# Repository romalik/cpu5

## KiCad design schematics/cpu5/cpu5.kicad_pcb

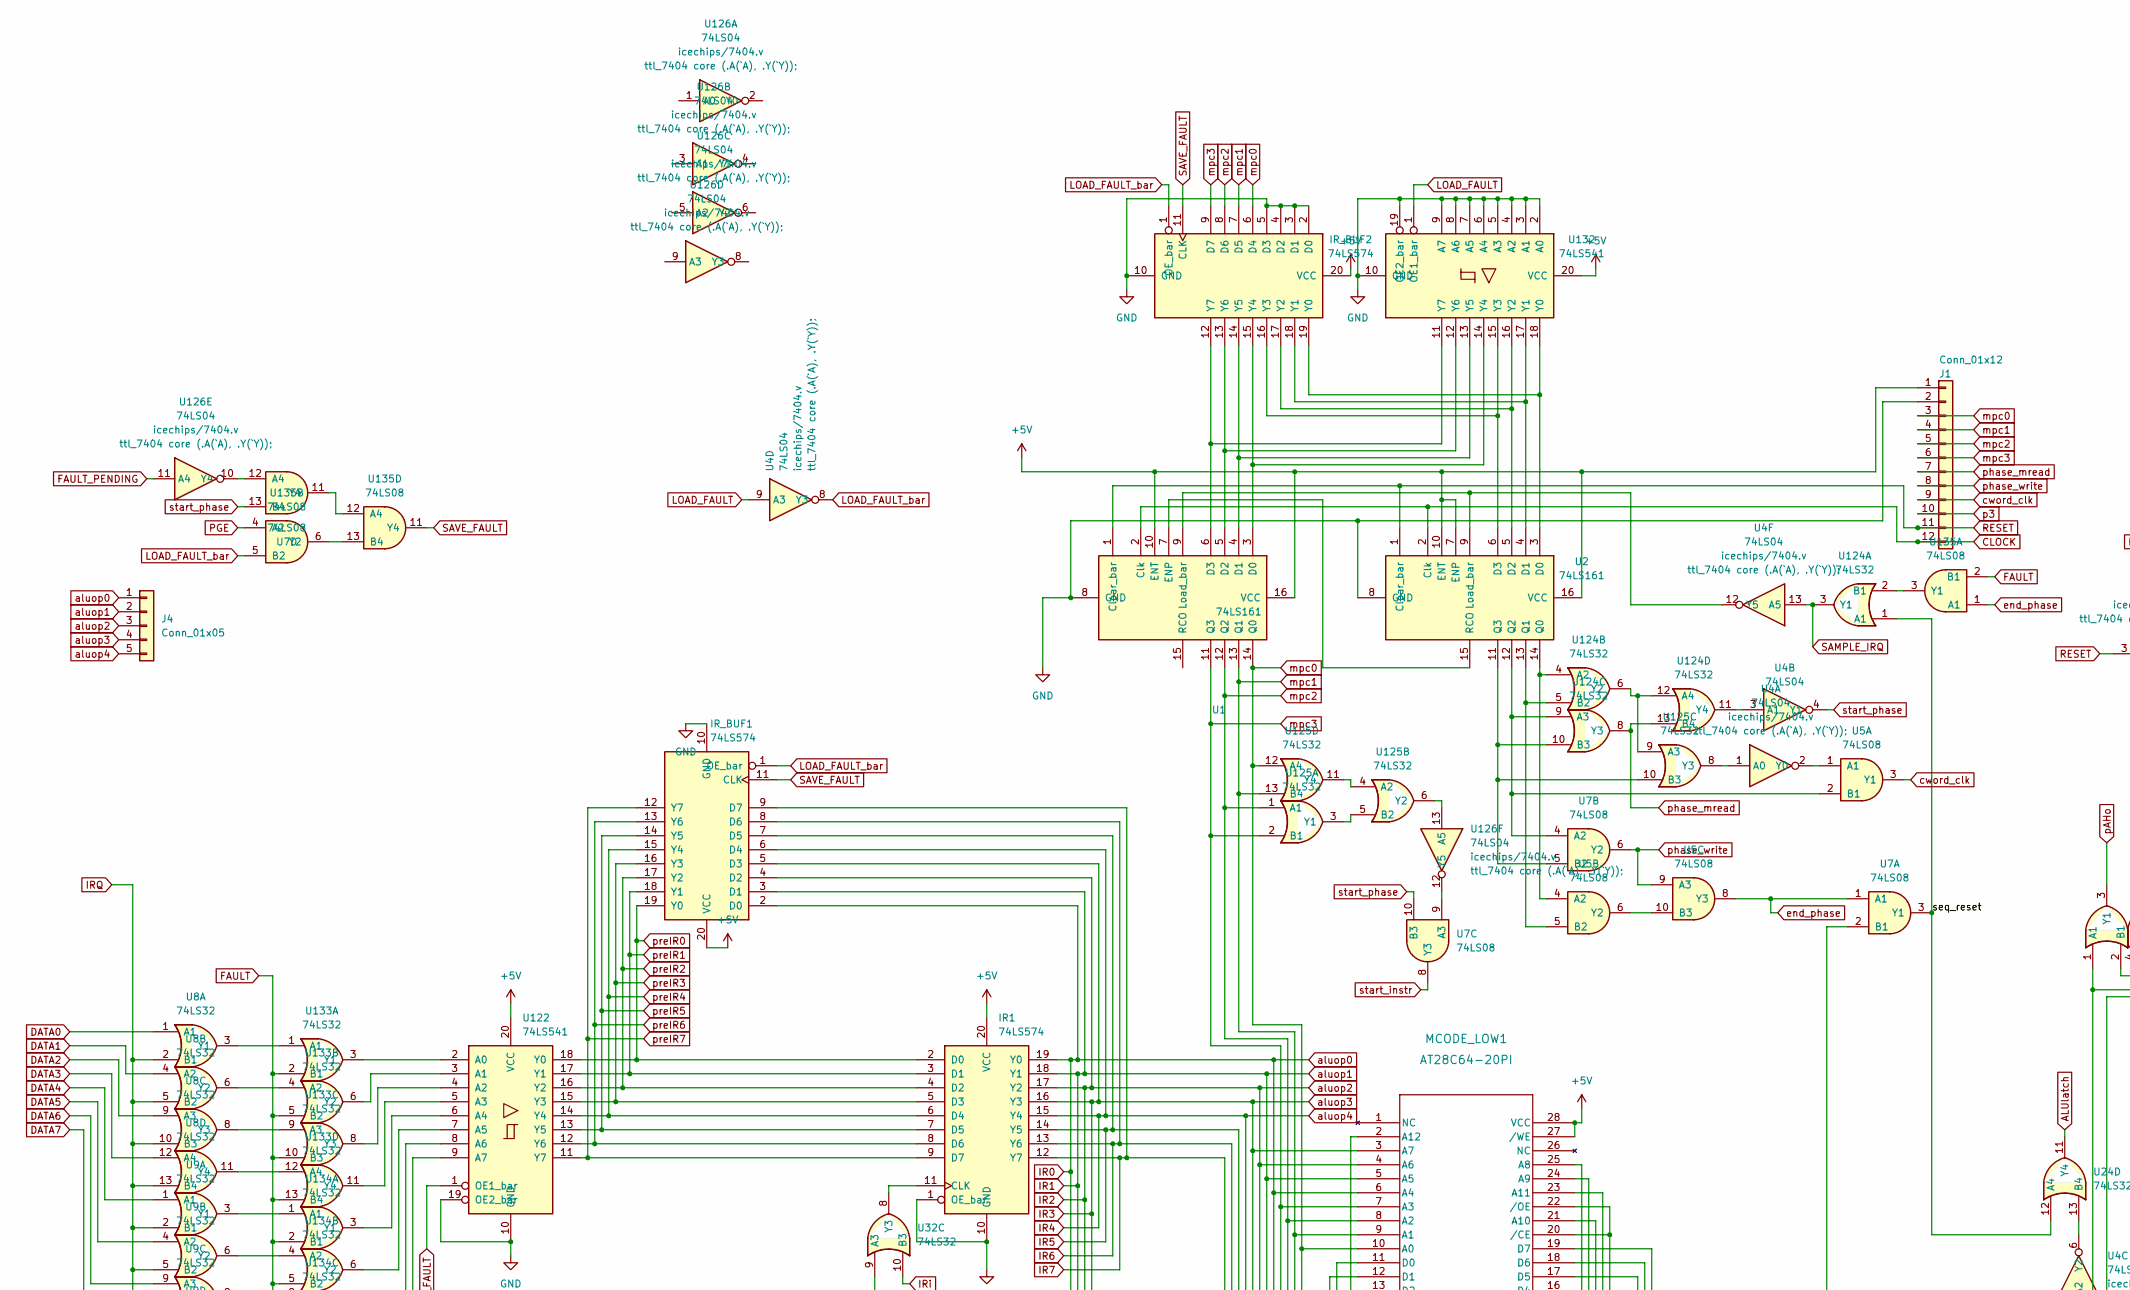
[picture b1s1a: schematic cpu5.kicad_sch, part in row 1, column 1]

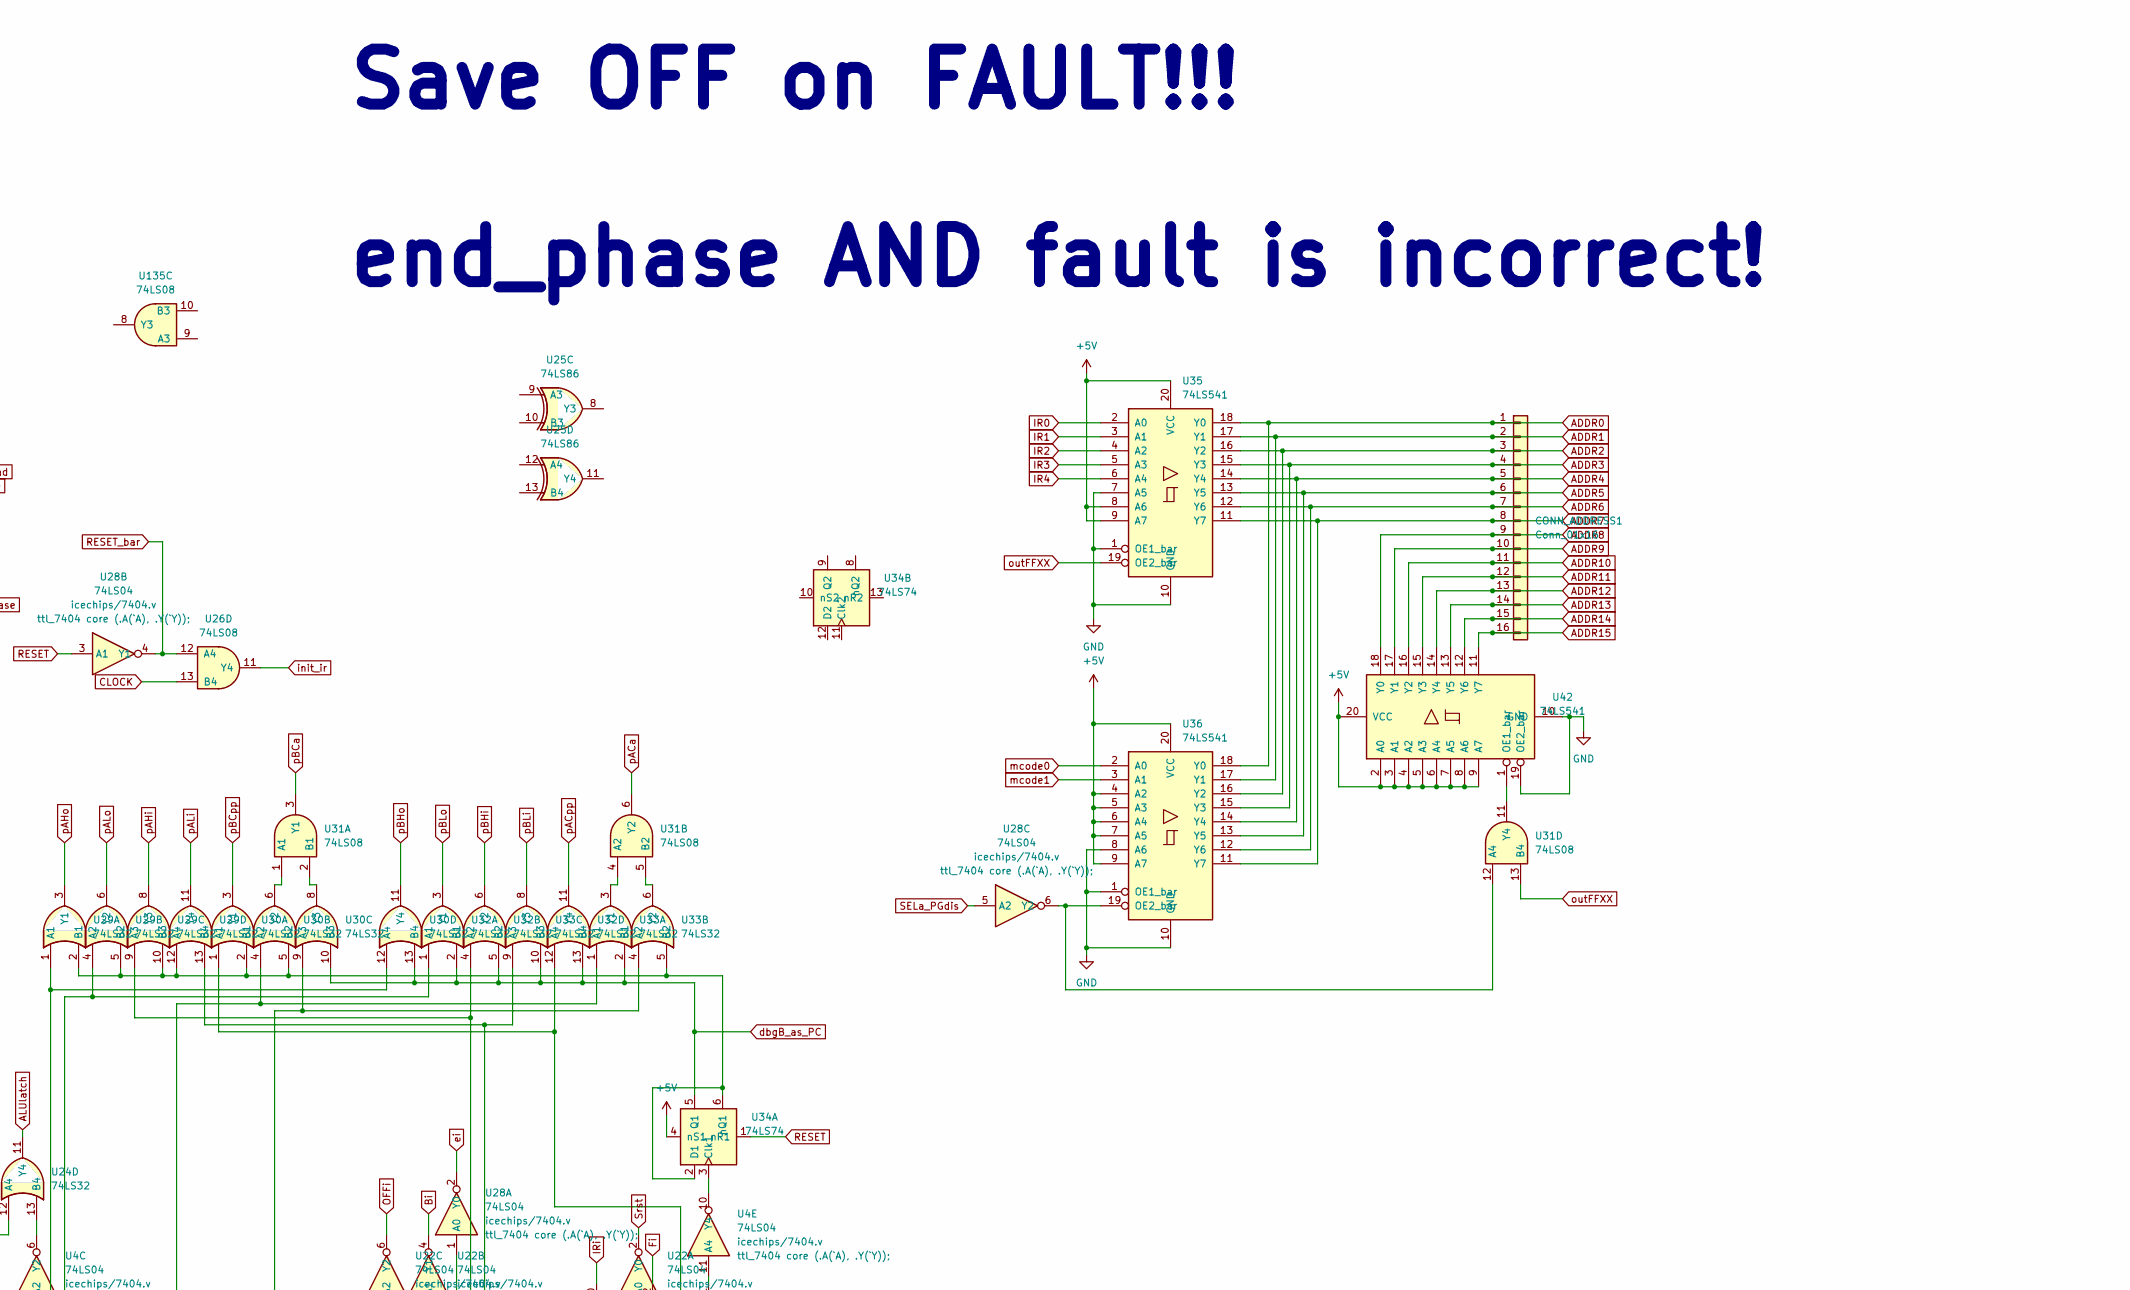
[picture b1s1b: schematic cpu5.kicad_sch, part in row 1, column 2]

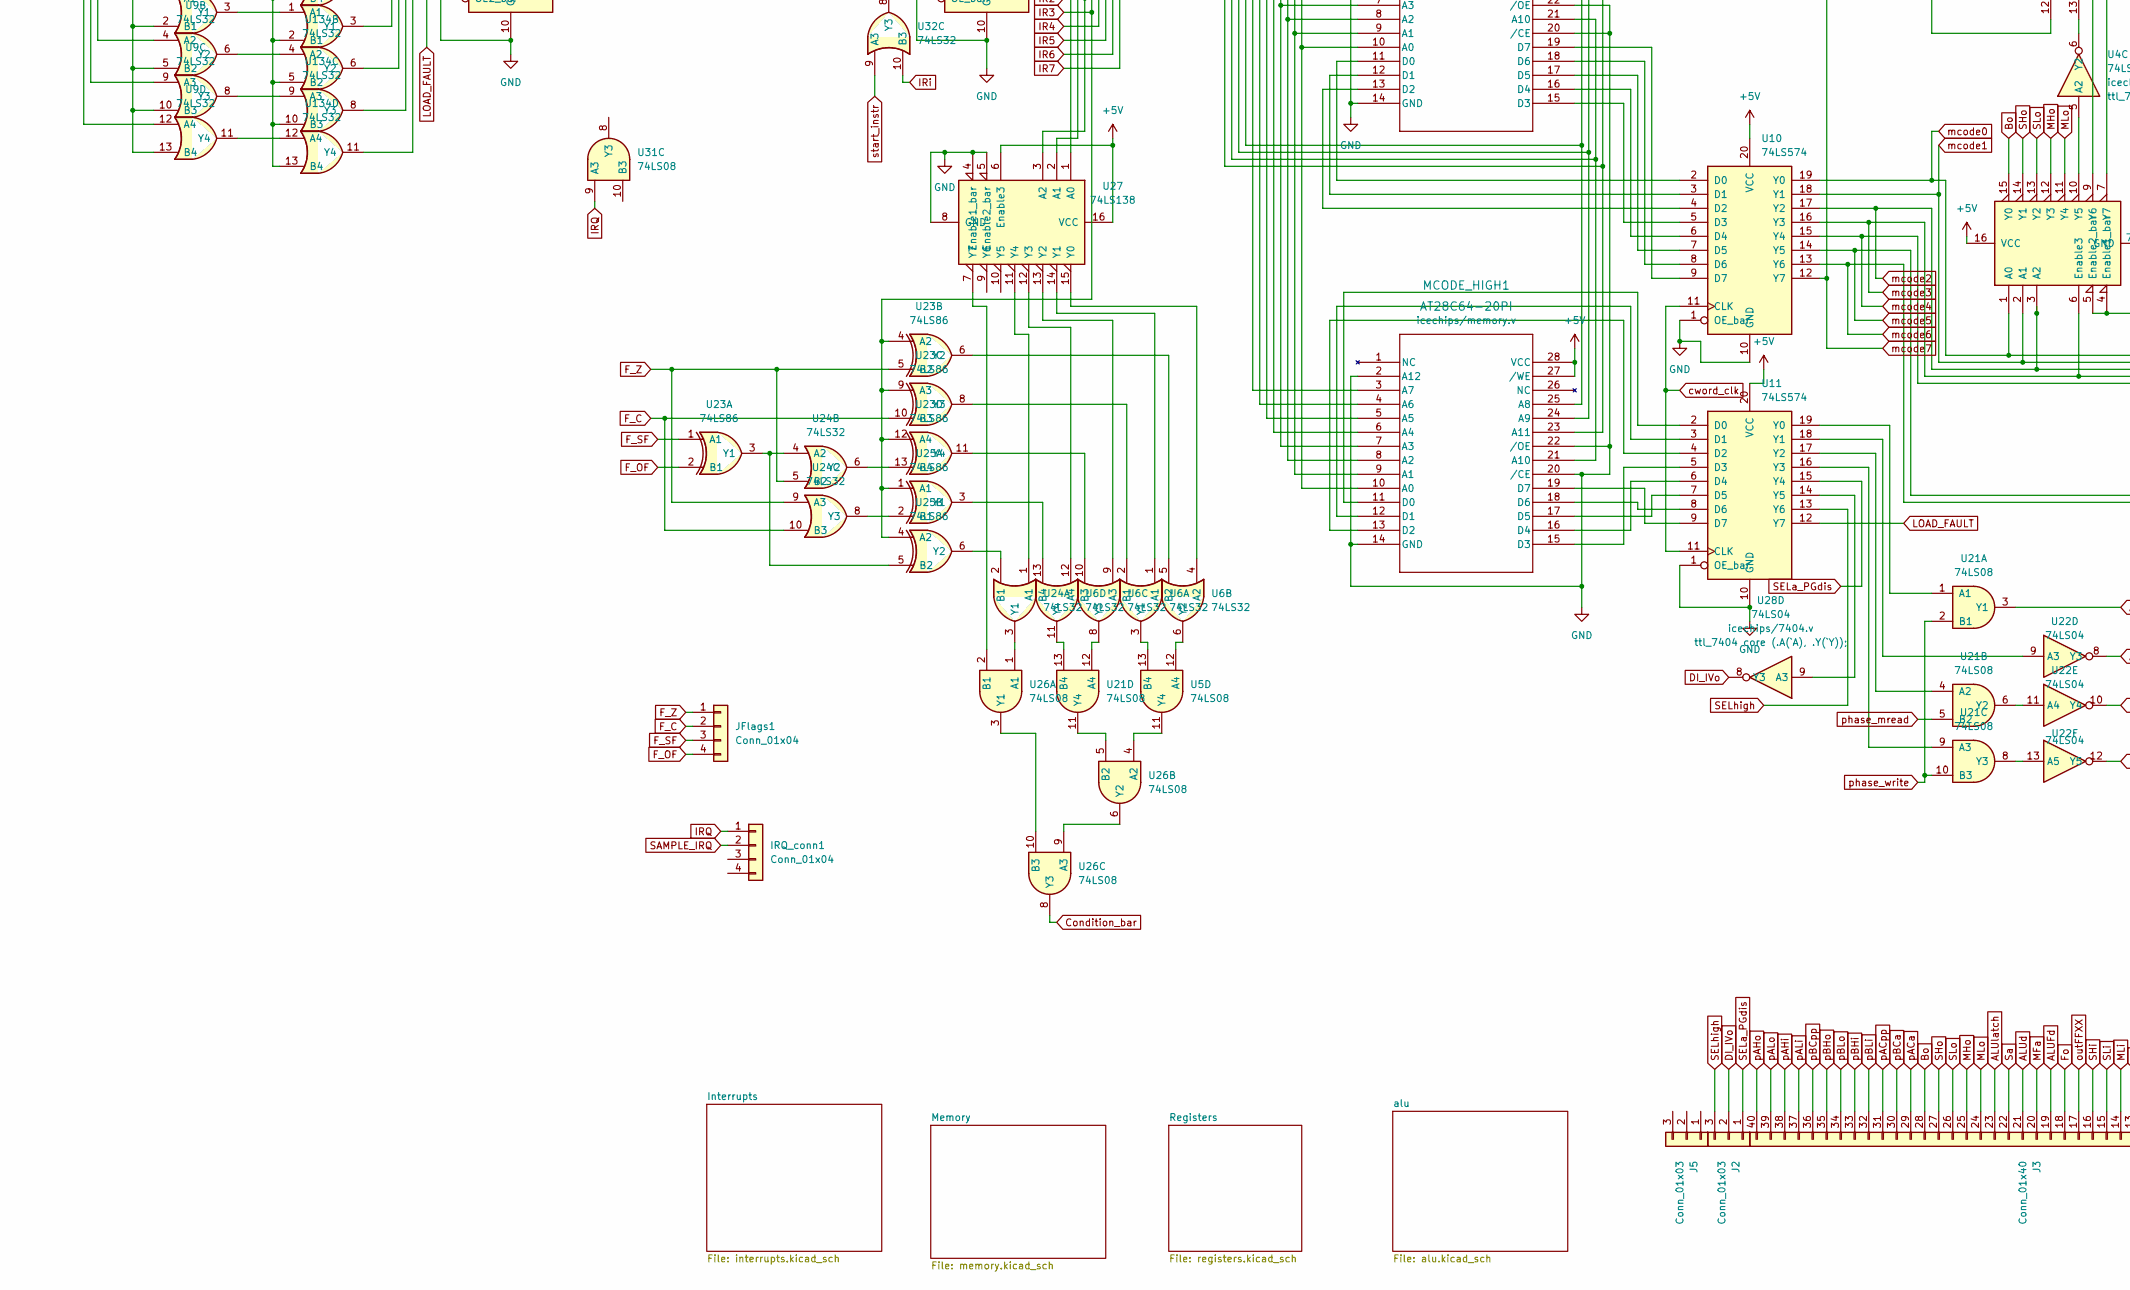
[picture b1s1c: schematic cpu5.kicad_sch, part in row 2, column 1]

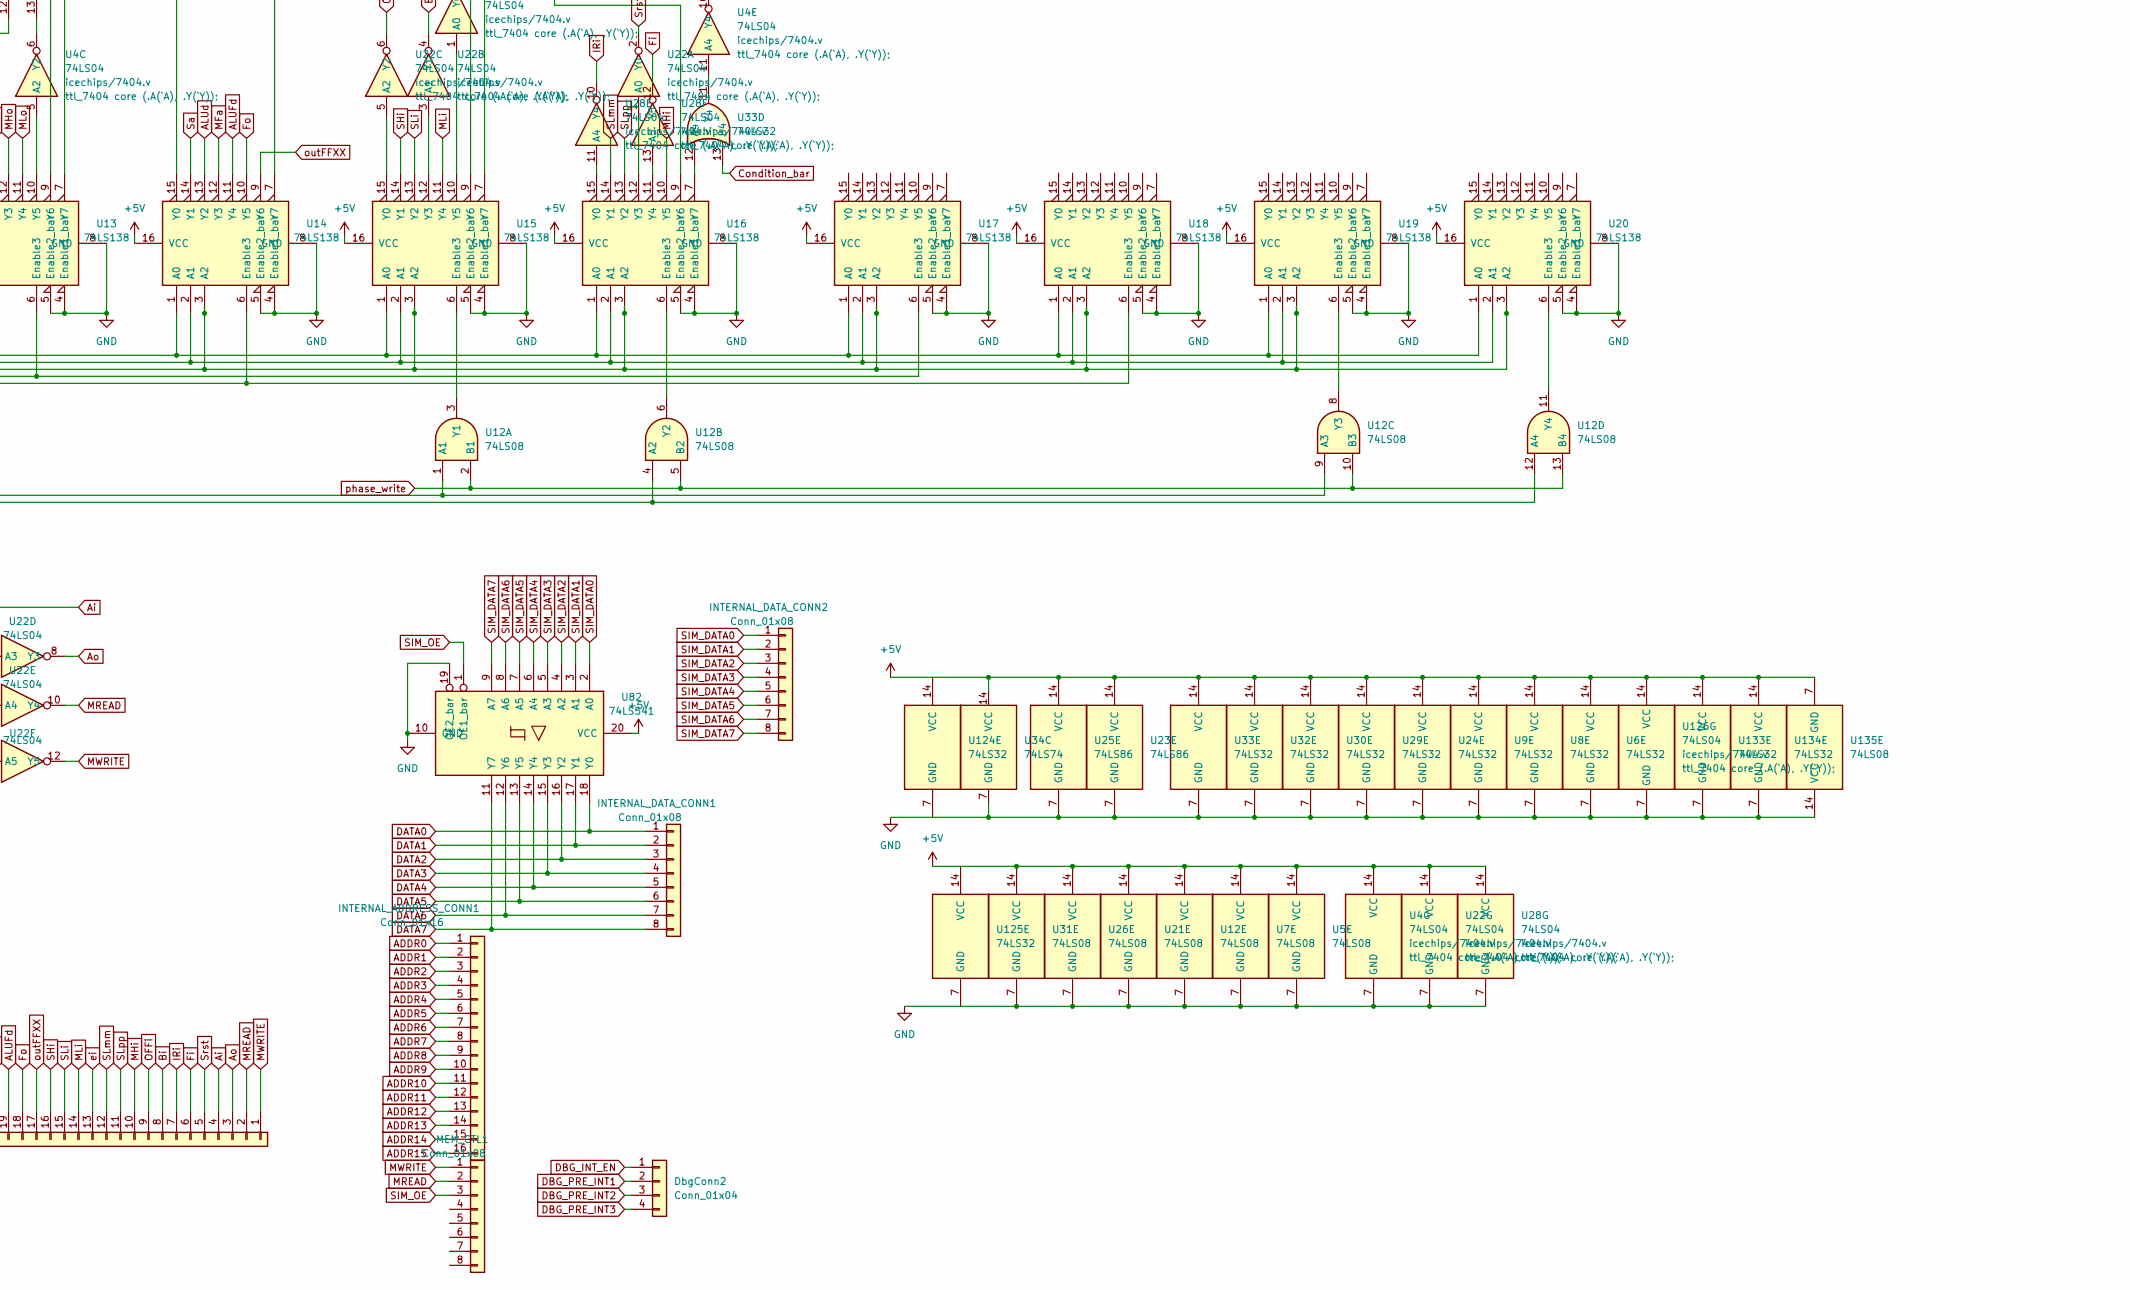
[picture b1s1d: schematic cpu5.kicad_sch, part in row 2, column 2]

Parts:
CONN_ADDRESS1: Conn_01x16; PinHeader_1x16_P2.54mm_Vertical
DbgConn2: Conn_01x04; PinHeader_1x04_P1.00mm_Vertical
INTERNAL_ADDRESS_CONN1: Conn_01x16; PinHeader_1x16_P2.54mm_Vertical
INTERNAL_DATA_CONN1, INTERNAL_DATA_CONN2: Conn_01x08; PinHeader_1x08_P2.54mm_Vertical
IR1: 74LS574; DIP-20_W7.62mm
IRQ_conn1: Conn_01x04; PinHeader_1x04_P1.00mm_Vertical
IR_BUF1, IR_BUF2: 74LS574; DIP-20_W7.62mm
J1: Conn_01x12; PinHeader_1x12_P2.54mm_Vertical
J2, J5: Conn_01x03; PinHeader_1x03_P2.54mm_Vertical
J3: Conn_01x40; PinHeader_1x40_P2.54mm_Vertical
J4: Conn_01x05; PinHeader_1x05_P2.54mm_Vertical
JFlags1: Conn_01x04; PinHeader_1x04_P1.00mm_Vertical
MCODE_HIGH1: AT28C64-20PI; DIP-28_W15.24mm
MCODE_LOW1: AT28C64-20PI; DIP-28_W15.24mm
MEM_CTL1: Conn_01x08; PinHeader_1x08_P2.54mm_Vertical
U1, U2: 74LS161; DIP-16_W7.62mm
U4, U22, U28, U126: 74LS04; DIP-14_W7.62mm
U5, U7, U12, U21, U26, U31, U135: 74LS08; DIP-14_W7.62mm
U6, U8, U9, U24, U29, U30, U32, U33, U124, U125, U133, U134: 74LS32; DIP-14_W7.62mm
U10, U11: 74LS574; DIP-20_W7.62mm
U13, U14, U15, U16, U17, U18, U19, U20, U27: 74LS138; DIP-16_W7.62mm
U23, U25: 74LS86; DIP-14_W7.62mm
U34: 74LS74; DIP-14_W7.62mm
U35, U36, U42, U82, U122, U132: 74LS541; DIP-20_W7.62mm

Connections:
+5V: IR1.20 (VCC), IR_BUF1.20 (VCC), IR_BUF2.20 (VCC), J1.1, MCODE_HIGH1.27 (/WE), MCODE_HIGH1.28 (VCC), MCODE_LOW1.27 (/WE), MCODE_LOW1.28 (VCC), U1.10 (ENT), U1.16 (VCC), U2.7 (ENP), U2.10 (ENT), U2.16 (VCC), U4.14 (VCC), U5.14 (VCC), U6.14 (VCC), U7.14 (VCC), U8.14 (VCC), U9.14 (VCC), U10.20 (VCC), U11.20 (VCC), U12.14 (VCC), U13.16 (VCC), U14.16 (VCC), U15.16 (VCC), U16.16 (VCC), U17.16 (VCC), U18.16 (VCC), U19.16 (VCC), U20.16 (VCC), U21.14 (VCC), U22.14 (VCC), U23.14 (VCC), U24.14 (VCC), U25.14 (VCC), U26.14 (VCC), U27.6 (Enable3), U27.16 (VCC), U28.14 (VCC), U29.14 (VCC), U30.14 (VCC), U31.14 (VCC), U32.14 (VCC), U33.14 (VCC), U34.4 (nS1), U34.14 (VCC), U35.8 (A6), U35.9 (A7), U35.20 (VCC), U36.4 (A2), U36.5 (A3), U36.6 (A4), U36.7 (A5), U36.9 (A7), U36.20 (VCC), U42.2 (A0), U42.3 (A1), U42.4 (A2), U42.5 (A3), U42.6 (A4), U42.7 (A5), U42.8 (A6), U42.9 (A7), U42.20 (VCC), U82.20 (VCC), U122.20 (VCC), U126.14 (VCC), U132.20 (VCC), U133.14 (VCC), U134.14 (VCC), U135.7 (GND); also elsewhere on the board
/seq_reset: U7.3 (Y1), U24.12 (A4), U124.1 (A1)
ADDR0: CONN_ADDRESS1.1, INTERNAL_ADDRESS_CONN1.1, U35.18 (Y0), U36.18 (Y0); also elsewhere on the board
ADDR1: CONN_ADDRESS1.2, INTERNAL_ADDRESS_CONN1.2, U35.17 (Y1), U36.17 (Y1); also elsewhere on the board
ADDR2: CONN_ADDRESS1.3, INTERNAL_ADDRESS_CONN1.3, U35.16 (Y2), U36.16 (Y2); also elsewhere on the board
ADDR3: CONN_ADDRESS1.4, INTERNAL_ADDRESS_CONN1.4, U35.15 (Y3), U36.15 (Y3); also elsewhere on the board
ADDR4: CONN_ADDRESS1.5, INTERNAL_ADDRESS_CONN1.5, U35.14 (Y4), U36.14 (Y4); also elsewhere on the board
ADDR5: CONN_ADDRESS1.6, INTERNAL_ADDRESS_CONN1.6, U35.13 (Y5), U36.13 (Y5); also elsewhere on the board
ADDR6: CONN_ADDRESS1.7, INTERNAL_ADDRESS_CONN1.7, U35.12 (Y6), U36.12 (Y6); also elsewhere on the board
ADDR7: CONN_ADDRESS1.8, INTERNAL_ADDRESS_CONN1.8, U35.11 (Y7), U36.11 (Y7); also elsewhere on the board
ADDR8: CONN_ADDRESS1.9, INTERNAL_ADDRESS_CONN1.9, U42.18 (Y0); also elsewhere on the board
ADDR9: CONN_ADDRESS1.10, INTERNAL_ADDRESS_CONN1.10, U42.17 (Y1); also elsewhere on the board
ADDR10: CONN_ADDRESS1.11, INTERNAL_ADDRESS_CONN1.11, U42.16 (Y2); also elsewhere on the board
ADDR11: CONN_ADDRESS1.12, INTERNAL_ADDRESS_CONN1.12, U42.15 (Y3); also elsewhere on the board
ADDR12: CONN_ADDRESS1.13, INTERNAL_ADDRESS_CONN1.13, U42.14 (Y4); also elsewhere on the board
ADDR13: CONN_ADDRESS1.14, INTERNAL_ADDRESS_CONN1.14, U42.13 (Y5); also elsewhere on the board
ADDR14: CONN_ADDRESS1.15, INTERNAL_ADDRESS_CONN1.15, U42.12 (Y6); also elsewhere on the board
ADDR15: CONN_ADDRESS1.16, INTERNAL_ADDRESS_CONN1.16, U42.11 (Y7); also elsewhere on the board
ALUFd: J3.19, U14.11 (Y4); also elsewhere on the board
ALUd: J3.21, U14.13 (Y2); also elsewhere on the board
ALUlatch: J3.23, U24.11 (Y4); also elsewhere on the board
Ai: J3.4, U21.3 (Y1); also elsewhere on the board
Ao: J3.3, U22.8 (Y3); also elsewhere on the board
Bi: J3.8, U22.4 (Y1); also elsewhere on the board
Bo: J3.28, U13.15 (Y0); also elsewhere on the board
CLOCK: J1.12, U1.2 (Clk), U2.2 (Clk), U26.13 (B4)
Condition_bar: U26.8 (Y3), U33.13 (B4)
DATA0: INTERNAL_DATA_CONN1.1, U8.1 (A1), U82.18 (Y0); also elsewhere on the board
DATA1: INTERNAL_DATA_CONN1.2, U8.4 (A2), U82.17 (Y1); also elsewhere on the board
DATA2: INTERNAL_DATA_CONN1.3, U8.9 (A3), U82.16 (Y2); also elsewhere on the board
DATA3: INTERNAL_DATA_CONN1.4, U8.12 (A4), U82.15 (Y3); also elsewhere on the board
DATA4: INTERNAL_DATA_CONN1.5, U9.1 (A1), U82.14 (Y4); also elsewhere on the board
DATA5: INTERNAL_DATA_CONN1.6, U9.4 (A2), U82.13 (Y5); also elsewhere on the board
DATA6: INTERNAL_DATA_CONN1.7, U9.9 (A3), U82.12 (Y6); also elsewhere on the board
DATA7: INTERNAL_DATA_CONN1.8, U9.12 (A4), U82.11 (Y7); also elsewhere on the board
DBG_INT_EN: DbgConn2.1; also elsewhere on the board
DBG_PRE_INT1: DbgConn2.2; also elsewhere on the board
DBG_PRE_INT2: DbgConn2.3; also elsewhere on the board
DBG_PRE_INT3: DbgConn2.4; also elsewhere on the board
DI_IVo: J2.2, U28.8 (Y3); also elsewhere on the board
FAULT: U133.2 (B1), U133.5 (B2), U133.10 (B3), U133.13 (B4), U134.2 (B1), U134.5 (B2), U134.10 (B3), U134.13 (B4), U135.2 (B1); also elsewhere on the board
FAULT_PENDING: U126.11 (A4); also elsewhere on the board
F_C: JFlags1.2, U23.10 (B3), U24.10 (B3); also elsewhere on the board
F_OF: JFlags1.4, U23.2 (B1); also elsewhere on the board
F_SF: JFlags1.3, U23.1 (A1); also elsewhere on the board
F_Z: JFlags1.1, U23.5 (B2), U24.5 (B2), U24.9 (A3); also elsewhere on the board
Fi: J3.6, U28.12 (Y5); also elsewhere on the board
Fo: J3.18, U14.10 (Y5); also elsewhere on the board
GND: IR1.1 (OE_bar), IR1.10 (GND), IR_BUF1.10 (GND), IR_BUF2.2 (D0), IR_BUF2.3 (D1), IR_BUF2.4 (D2), IR_BUF2.5 (D3), IR_BUF2.10 (GND), J1.2, MCODE_HIGH1.2 (A12), MCODE_HIGH1.14 (GND), MCODE_HIGH1.20 (/CE), MCODE_HIGH1.22 (/OE), MCODE_LOW1.2 (A12), MCODE_LOW1.14 (GND), MCODE_LOW1.20 (/CE), MCODE_LOW1.22 (/OE), U1.8 (GND), U2.8 (GND), U4.7 (GND), U5.7 (GND), U6.7 (GND), U7.7 (GND), U8.7 (GND), U9.7 (GND), U10.1 (OE_bar), U10.10 (GND), U11.1 (OE_bar), U11.10 (GND), U12.7 (GND), U13.4 (Enable1_bar), U13.5 (Enable2_bar), U13.8 (GND), U14.4 (Enable1_bar), U14.5 (Enable2_bar), U14.8 (GND), U15.4 (Enable1_bar), U15.5 (Enable2_bar), U15.8 (GND), U16.4 (Enable1_bar), U16.5 (Enable2_bar), U16.8 (GND), U17.4 (Enable1_bar), U17.5 (Enable2_bar), U17.8 (GND), U18.4 (Enable1_bar), U18.5 (Enable2_bar), U18.8 (GND), U19.4 (Enable1_bar), U19.5 (Enable2_bar), U19.8 (GND), U20.4 (Enable1_bar), U20.5 (Enable2_bar), U20.8 (GND), U21.7 (GND), U22.7 (GND), U23.7 (GND), U24.7 (GND), U25.7 (GND), U26.7 (GND), U27.4 (Enable1_bar), U27.5 (Enable2_bar), U27.8 (GND), U28.7 (GND), U29.7 (GND), U30.7 (GND), U31.7 (GND), U32.7 (GND), U33.7 (GND), U34.7 (GND), U35.1 (OE1_bar), U35.7 (A5), U35.10 (GND), U36.1 (OE1_bar), U36.8 (A6), U36.10 (GND), U42.10 (GND), U42.19 (OE2_bar), U82.10 (GND), U82.19 (OE2_bar), U122.10 (GND), U122.19 (OE2_bar), U126.7 (GND), U132.2 (A0), U132.3 (A1), U132.4 (A2), U132.5 (A3), U132.6 (A4), U132.7 (A5), U132.8 (A6), U132.9 (A7), U132.10 (GND), U132.19 (OE2_bar), U133.7 (GND), U134.7 (GND), U135.14 (VCC); also elsewhere on the board
IR0: IR1.19 (Y0), IR_BUF1.2 (D0), J4.1, MCODE_HIGH1.6 (A4), MCODE_LOW1.6 (A4), U27.1 (A0), U35.2 (A0); also elsewhere on the board
IR1: IR1.18 (Y1), IR_BUF1.3 (D1), J4.2, MCODE_HIGH1.5 (A5), MCODE_LOW1.5 (A5), U27.2 (A1), U35.3 (A1); also elsewhere on the board
IR2: IR1.17 (Y2), IR_BUF1.4 (D2), J4.3, MCODE_HIGH1.4 (A6), MCODE_LOW1.4 (A6), U27.3 (A2), U35.4 (A2); also elsewhere on the board
IR3: IR1.16 (Y3), IR_BUF1.5 (D3), J4.4, MCODE_HIGH1.3 (A7), MCODE_LOW1.3 (A7), U23.4 (A2), U23.9 (A3), U23.12 (A4), U25.1 (A1), U25.4 (A2), U35.5 (A3); also elsewhere on the board
IR4: IR1.15 (Y4), IR_BUF1.6 (D4), J4.5, MCODE_HIGH1.25 (A8), MCODE_LOW1.25 (A8), U35.6 (A4); also elsewhere on the board
IR5: IR1.14 (Y5), IR_BUF1.7 (D5), MCODE_HIGH1.24 (A9), MCODE_LOW1.24 (A9)
IR6: IR1.13 (Y6), IR_BUF1.8 (D6), MCODE_HIGH1.21 (A10), MCODE_LOW1.21 (A10)
IR7: IR1.12 (Y7), IR_BUF1.9 (D7), MCODE_HIGH1.23 (A11), MCODE_LOW1.23 (A11)
IRQ: IRQ_conn1.1, U8.2 (B1), U8.5 (B2), U8.10 (B3), U8.13 (B4), U9.2 (B1), U9.5 (B2), U9.10 (B3), U9.13 (B4), U31.9 (A3); also elsewhere on the board
IRi: J3.7, U28.10 (Y4), U32.10 (B3)
LOAD_FAULT: U4.9 (A3), U11.12 (Y7), U122.1 (OE1_bar), U132.1 (OE1_bar); also elsewhere on the board
LOAD_FAULT_bar: IR_BUF1.1 (OE_bar), IR_BUF2.1 (OE_bar), U4.8 (Y3), U135.5 (B2); also elsewhere on the board
MFa: J3.20, U14.12 (Y3); also elsewhere on the board
MHi: J3.10, U16.10 (Y5); also elsewhere on the board
MHo: J3.25, U13.12 (Y3); also elsewhere on the board
MLi: J3.14, U15.11 (Y4); also elsewhere on the board
MLo: J3.24, U13.11 (Y4); also elsewhere on the board
MREAD: J3.2, MEM_CTL1.2, U22.10 (Y4); also elsewhere on the board
MWRITE: J3.1, MEM_CTL1.1, U22.12 (Y5); also elsewhere on the board
unnamed: IR1.11 (CLK), U32.8 (Y3)
unnamed: IR_BUF2.12 (Y7), U1.6 (D3), U132.11 (Y7)
unnamed: IR_BUF2.13 (Y6), U1.5 (D2), U132.12 (Y6)
unnamed: IR_BUF2.14 (Y5), U1.4 (D1), U132.13 (Y5)
unnamed: IR_BUF2.15 (Y4), U1.3 (D0), U132.14 (Y4)
unnamed: IR_BUF2.16 (Y3), U2.6 (D3), U132.15 (Y3)
unnamed: IR_BUF2.17 (Y2), U2.5 (D2), U132.16 (Y2)
unnamed: IR_BUF2.18 (Y1), U2.4 (D1), U132.17 (Y1)
unnamed: IR_BUF2.19 (Y0), U2.3 (D0), U132.18 (Y0)
unnamed: MCODE_HIGH1.11 (D0), U11.2 (D0)
unnamed: MCODE_HIGH1.12 (D1), U11.3 (D1)
unnamed: MCODE_HIGH1.13 (D2), U11.4 (D2)
unnamed: MCODE_HIGH1.15 (D3), U11.5 (D3)
unnamed: MCODE_HIGH1.16 (D4), U11.6 (D4)
unnamed: MCODE_HIGH1.17 (D5), U11.7 (D5)
unnamed: MCODE_HIGH1.18 (D6), U11.8 (D6)
unnamed: MCODE_HIGH1.19 (D7), U11.9 (D7)
unnamed: MCODE_LOW1.11 (D0), U10.2 (D0)
unnamed: MCODE_LOW1.12 (D1), U10.3 (D1)
unnamed: MCODE_LOW1.13 (D2), U10.4 (D2)
unnamed: MCODE_LOW1.15 (D3), U10.5 (D3)
unnamed: MCODE_LOW1.16 (D4), U10.6 (D4)
unnamed: MCODE_LOW1.17 (D5), U10.7 (D5)
unnamed: MCODE_LOW1.18 (D6), U10.8 (D6)
unnamed: MCODE_LOW1.19 (D7), U10.9 (D7)
unnamed: U1.7 (ENP), U2.15 (RCO)
unnamed: U1.9 (Load_bar), U2.9 (Load_bar), U4.12 (Y5)
unnamed: U4.2 (Y0), U5.1 (A1)
unnamed: U5.6 (Y2), U5.10 (B3)
unnamed: U5.12 (A4), U6.6 (Y2)
unnamed: U5.13 (B4), U6.3 (Y1)
unnamed: U11.14 (Y5), U28.9 (A3)
unnamed: U11.16 (Y3), U21.9 (A3)
unnamed: U11.17 (Y2), U21.4 (A2)
unnamed: U11.18 (Y1), U22.9 (A3)
unnamed: U11.19 (Y0), U21.1 (A1)
unnamed: U12.3 (Y1), U15.6 (Enable3)
unnamed: U12.6 (Y2), U16.6 (Enable3)
unnamed: U12.8 (Y3), U19.6 (Enable3)
unnamed: U12.11 (Y4), U20.6 (Enable3)
unnamed: U13.7 (Y7), U29.4 (A2), U32.1 (A1)
unnamed: U13.9 (Y6), U29.1 (A1), U30.12 (A4)
unnamed: U4.5 (A2), U13.10 (Y5)
unnamed: U14.7 (Y7), U30.9 (A3), U33.4 (A2)
unnamed: U14.15 (Y0), U30.4 (A2), U33.1 (A1)
unnamed: U15.7 (Y7), U29.13 (B4), U33.9 (A3)
unnamed: U15.9 (Y6), U29.9 (A3), U32.4 (A2)
unnamed: U15.10 (Y5), U28.1 (A0)
unnamed: U15.12 (Y3), U22.3 (A1)
unnamed: U15.15 (Y0), U22.5 (A2)
unnamed: U16.7 (Y7), U33.12 (A4)
unnamed: U16.9 (Y6), U30.1 (A1), U32.12 (A4)
unnamed: U16.11 (Y4), U28.13 (A5)
unnamed: U16.12 (Y3), U22.1 (A0)
unnamed: U16.15 (Y0), U28.11 (A4)
unnamed: U21.6 (Y2), U22.11 (A4)
unnamed: U21.8 (Y3), U22.13 (A5)
unnamed: U21.11 (Y4), U26.5 (B2)
unnamed: U6.8 (Y3), U21.12 (A4)
unnamed: U6.11 (Y4), U21.13 (B4)
unnamed: U23.3 (Y1), U24.4 (A2), U25.5 (B2)
unnamed: U6.5 (B2), U23.6 (Y2)
unnamed: U6.2 (B1), U23.8 (Y3)
unnamed: U6.10 (B3), U23.11 (Y4)
unnamed: U23.13 (B4), U24.6 (Y2)
unnamed: U24.1 (A1), U27.11 (Y4)
unnamed: U24.2 (B1), U25.6 (Y2)
unnamed: U24.3 (Y1), U26.1 (A1)
unnamed: U24.8 (Y3), U25.2 (B1)
unnamed: U4.6 (Y2), U24.13 (B4)
unnamed: U6.13 (B4), U25.3 (Y1)
unnamed: U26.2 (B1), U27.7 (Y7)
unnamed: U5.11 (Y4), U26.4 (A2)
unnamed: U26.6 (Y2), U26.9 (A3)
unnamed: U26.3 (Y1), U26.10 (B3)
unnamed: U6.12 (A4), U27.12 (Y3)
unnamed: U6.9 (A3), U27.13 (Y2)
unnamed: U6.1 (A1), U27.14 (Y1)
unnamed: U6.4 (A2), U27.15 (Y0)
unnamed: U28.6 (Y2), U31.12 (A4), U36.19 (OE2_bar)
unnamed: U29.2 (B1), U29.5 (B2), U29.10 (B3), U29.12 (A4), U30.2 (B1), U30.5 (B2), U33.5 (B2), U34.2 (D1), U34.6 (nQ1)
unnamed: U30.6 (Y2), U31.1 (A1)
unnamed: U30.8 (Y3), U31.2 (B1)
unnamed: U31.4 (A2), U33.3 (Y1)
unnamed: U31.5 (B2), U33.6 (Y2)
unnamed: U31.11 (Y4), U42.1 (OE1_bar)
unnamed: U4.11 (A4), U33.11 (Y4)
unnamed: U4.10 (Y4), U34.3 (Clk1)
unnamed: U122.2 (A0), U133.3 (Y1)
unnamed: U122.3 (A1), U133.6 (Y2)
unnamed: U122.4 (A2), U133.8 (Y3)
unnamed: U122.5 (A3), U133.11 (Y4)
unnamed: U122.6 (A4), U134.3 (Y1)
unnamed: U122.7 (A5), U134.6 (Y2)
unnamed: U122.8 (A6), U134.8 (Y3)
unnamed: U122.9 (A7), U134.11 (Y4)
unnamed: U124.2 (B1), U135.3 (Y1)
unnamed: U2.14 (Q0), U5.4 (A2), U124.4 (A2)
unnamed: U2.13 (Q1), U5.5 (B2), U124.5 (B2)
unnamed: U2.12 (Q2), U5.2 (B1), U7.4 (A2), U124.9 (A3)
unnamed: U2.11 (Q3), U7.5 (B2), U124.10 (B3), U125.10 (B3)
unnamed: U4.3 (A1), U124.11 (Y4)
unnamed: U124.6 (Y2), U124.12 (A4), U125.9 (A3)
unnamed: U125.3 (Y1), U125.5 (B2)
unnamed: U125.6 (Y2), U126.13 (A5)
unnamed: U4.1 (A0), U125.8 (Y3)
unnamed: U125.4 (A2), U125.11 (Y4)
unnamed: U7.12 (A4), U126.10 (Y4)
unnamed: U7.9 (A3), U126.12 (Y5)
unnamed: U8.3 (Y1), U133.1 (A1)
unnamed: U8.6 (Y2), U133.4 (A2)
unnamed: U8.8 (Y3), U133.9 (A3)
unnamed: U8.11 (Y4), U133.12 (A4)
unnamed: U9.3 (Y1), U134.1 (A1)
unnamed: U9.6 (Y2), U134.4 (A2)
unnamed: U9.8 (Y3), U134.9 (A3)
unnamed: U9.11 (Y4), U134.12 (A4)
unnamed: U7.11 (Y4), U135.12 (A4)
unnamed: U135.6 (Y2), U135.13 (B4)
OFFi: J3.9, U22.6 (Y2); also elsewhere on the board
PGE: U135.4 (A2); also elsewhere on the board
RESET: J1.11, U1.1 (Clear_bar), U2.1 (Clear_bar), U28.3 (A1), U34.1 (nR1); also elsewhere on the board
RESET_bar: U26.12 (A4), U28.4 (Y1); also elsewhere on the board
SAMPLE_IRQ: IRQ_conn1.2, U4.13 (A5), U124.3 (Y1); also elsewhere on the board
SAVE_FAULT: IR_BUF1.11 (CLK), IR_BUF2.11 (CLK), U135.11 (Y4); also elsewhere on the board
SELa_PGdis: J2.1, U11.15 (Y4), U28.5 (A2); also elsewhere on the board
SELhigh: J2.3, U11.13 (Y6); also elsewhere on the board
SHi: J3.16, U15.14 (Y1); also elsewhere on the board
SHo: J3.27, U13.14 (Y1); also elsewhere on the board
SIM_DATA0: INTERNAL_DATA_CONN2.1, U82.2 (A0)
SIM_DATA1: INTERNAL_DATA_CONN2.2, U82.3 (A1)
SIM_DATA2: INTERNAL_DATA_CONN2.3, U82.4 (A2)
SIM_DATA3: INTERNAL_DATA_CONN2.4, U82.5 (A3)
SIM_DATA4: INTERNAL_DATA_CONN2.5, U82.6 (A4)
SIM_DATA5: INTERNAL_DATA_CONN2.6, U82.7 (A5)
SIM_DATA6: INTERNAL_DATA_CONN2.7, U82.8 (A6)
SIM_DATA7: INTERNAL_DATA_CONN2.8, U82.9 (A7)
SIM_OE: MEM_CTL1.3, U82.1 (OE1_bar)
SLi: J3.15, U15.13 (Y2); also elsewhere on the board
SLmm: J3.12, U16.14 (Y1); also elsewhere on the board
SLo: J3.26, U13.13 (Y2); also elsewhere on the board
SLpp: J3.11, U16.13 (Y2); also elsewhere on the board
Sa: J3.22, U14.14 (Y1); also elsewhere on the board
Srst: J3.5, U22.2 (Y0); also elsewhere on the board
cword_clk: J1.9, U5.3 (Y1), U10.11 (CLK), U11.11 (CLK)
dbgB_as_PC: U30.10 (B3), U30.13 (B4), U32.2 (B1), U32.5 (B2), U32.13 (B4), U33.2 (B1), U33.10 (B3), U34.5 (Q1)
ei: J3.13, U28.2 (Y0); also elsewhere on the board
end_phase: U5.8 (Y3), U7.1 (A1), U135.1 (A1)
init_ir: U26.11 (Y4)
mcode0: U10.19 (Y0), U13.1 (A0), U14.1 (A0), U15.1 (A0), U16.1 (A0), U17.1 (A0), U18.1 (A0), U19.1 (A0), U20.1 (A0), U36.2 (A0)
mcode1: U10.18 (Y1), U13.2 (A1), U14.2 (A1), U15.2 (A1), U16.2 (A1), U17.2 (A1), U18.2 (A1), U19.2 (A1), U20.2 (A1), U36.3 (A1)
mcode2: U10.17 (Y2), U13.3 (A2), U14.3 (A2), U15.3 (A2), U16.3 (A2), U17.3 (A2), U18.3 (A2), U19.3 (A2), U20.3 (A2)
mcode3: U10.16 (Y3), U13.6 (Enable3), U17.6 (Enable3)
mcode4: U10.15 (Y4), U14.6 (Enable3), U18.6 (Enable3)
mcode5: U10.14 (Y5), U12.1 (A1), U12.9 (A3)
mcode6: U10.13 (Y6), U12.4 (A2), U12.12 (A4)
mcode7: U7.2 (B1), U10.12 (Y7)
mpc0: IR_BUF2.6 (D4), J1.3, MCODE_HIGH1.10 (A0), MCODE_LOW1.10 (A0), U1.14 (Q0), U125.12 (A4)
mpc1: IR_BUF2.7 (D5), J1.4, MCODE_HIGH1.9 (A1), MCODE_LOW1.9 (A1), U1.13 (Q1), U125.13 (B4)
mpc2: IR_BUF2.8 (D6), J1.5, MCODE_HIGH1.8 (A2), MCODE_LOW1.8 (A2), U1.12 (Q2), U125.1 (A1)
mpc3: IR_BUF2.9 (D7), J1.6, MCODE_HIGH1.7 (A3), MCODE_LOW1.7 (A3), U1.11 (Q3), U125.2 (B1)
outFFXX: J3.17, U14.9 (Y6), U31.13 (B4), U35.19 (OE2_bar)
p3: J1.10
pACa: J3.29, U31.6 (Y2); also elsewhere on the board
pACpp: J3.31, U32.11 (Y4); also elsewhere on the board
pAHi: J3.38, U29.8 (Y3); also elsewhere on the board
pAHo: J3.40, U29.3 (Y1); also elsewhere on the board
pALi: J3.37, U29.11 (Y4); also elsewhere on the board
pALo: J3.39, U29.6 (Y2); also elsewhere on the board
pBCa: J3.30, U31.3 (Y1); also elsewhere on the board
pBCpp: J3.36, U30.3 (Y1); also elsewhere on the board
pBHi: J3.33, U32.6 (Y2); also elsewhere on the board
pBHo: J3.35, U30.11 (Y4); also elsewhere on the board
pBLi: J3.32, U33.8 (Y3); also elsewhere on the board
pBLo: J3.34, U32.3 (Y1); also elsewhere on the board
phase_mread: J1.7, U21.5 (B2), U124.8 (Y3), U124.13 (B4)
phase_write: J1.8, U5.9 (A3), U7.6 (Y2), U12.2 (B1), U12.5 (B2), U12.10 (B3), U12.13 (B4), U21.2 (B1), U21.10 (B3)
preIR0: IR1.2 (D0), IR_BUF1.19 (Y0), U122.18 (Y0)
preIR1: IR1.3 (D1), IR_BUF1.18 (Y1), U122.17 (Y1)
preIR2: IR1.4 (D2), IR_BUF1.17 (Y2), U122.16 (Y2)
preIR3: IR1.5 (D3), IR_BUF1.16 (Y3), U122.15 (Y3)
preIR4: IR1.6 (D4), IR_BUF1.15 (Y4), U122.14 (Y4)
preIR5: IR1.7 (D5), IR_BUF1.14 (Y5), U122.13 (Y5)
preIR6: IR1.8 (D6), IR_BUF1.13 (Y6), U122.12 (Y6)
preIR7: IR1.9 (D7), IR_BUF1.12 (Y7), U122.11 (Y7)
start_instr: U7.8 (Y3), U32.9 (A3)
start_phase: U4.4 (Y1), U7.10 (B3), U7.13 (B4); also elsewhere on the board

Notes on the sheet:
Save OFF on FAULT!!! end_phase AND fault is incorrect!
